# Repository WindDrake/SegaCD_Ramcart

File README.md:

# SegaCD_Ramcart
 Sega Genesis/Megadrive CD Back-up RAM Cart

 Design done in Kicad 5.1.10 with Digikey libraries. If you want to edit it, you'll need those libraries as well as these files.

 Board tested working 9/3/21 after fixing A20/A22 accidental swap @ U4.

 PCB revision 1.1 has this fixed.
 PCB revision 1.2 adds R2 to make sure the SRAM goes into sleep mode. The BOM has also changed.

 RAM Cart tested 9/3 with Dark Wizard and does not have the save corruption issue that the Castlemania Ultra cart has.

 CSV Format BOM & Gerbers added 10/30/21.

 If you have an Etsy/eBay/Aliexpress/etc. cartridge and are experiencing low battery life, you'll need to swap parts at R1, D1, and U2 with the parts listed in the current BOM. You'll also need to add a 10k resistor from U2 Pin 22 to D1 Pin 3 (the single pin on top).

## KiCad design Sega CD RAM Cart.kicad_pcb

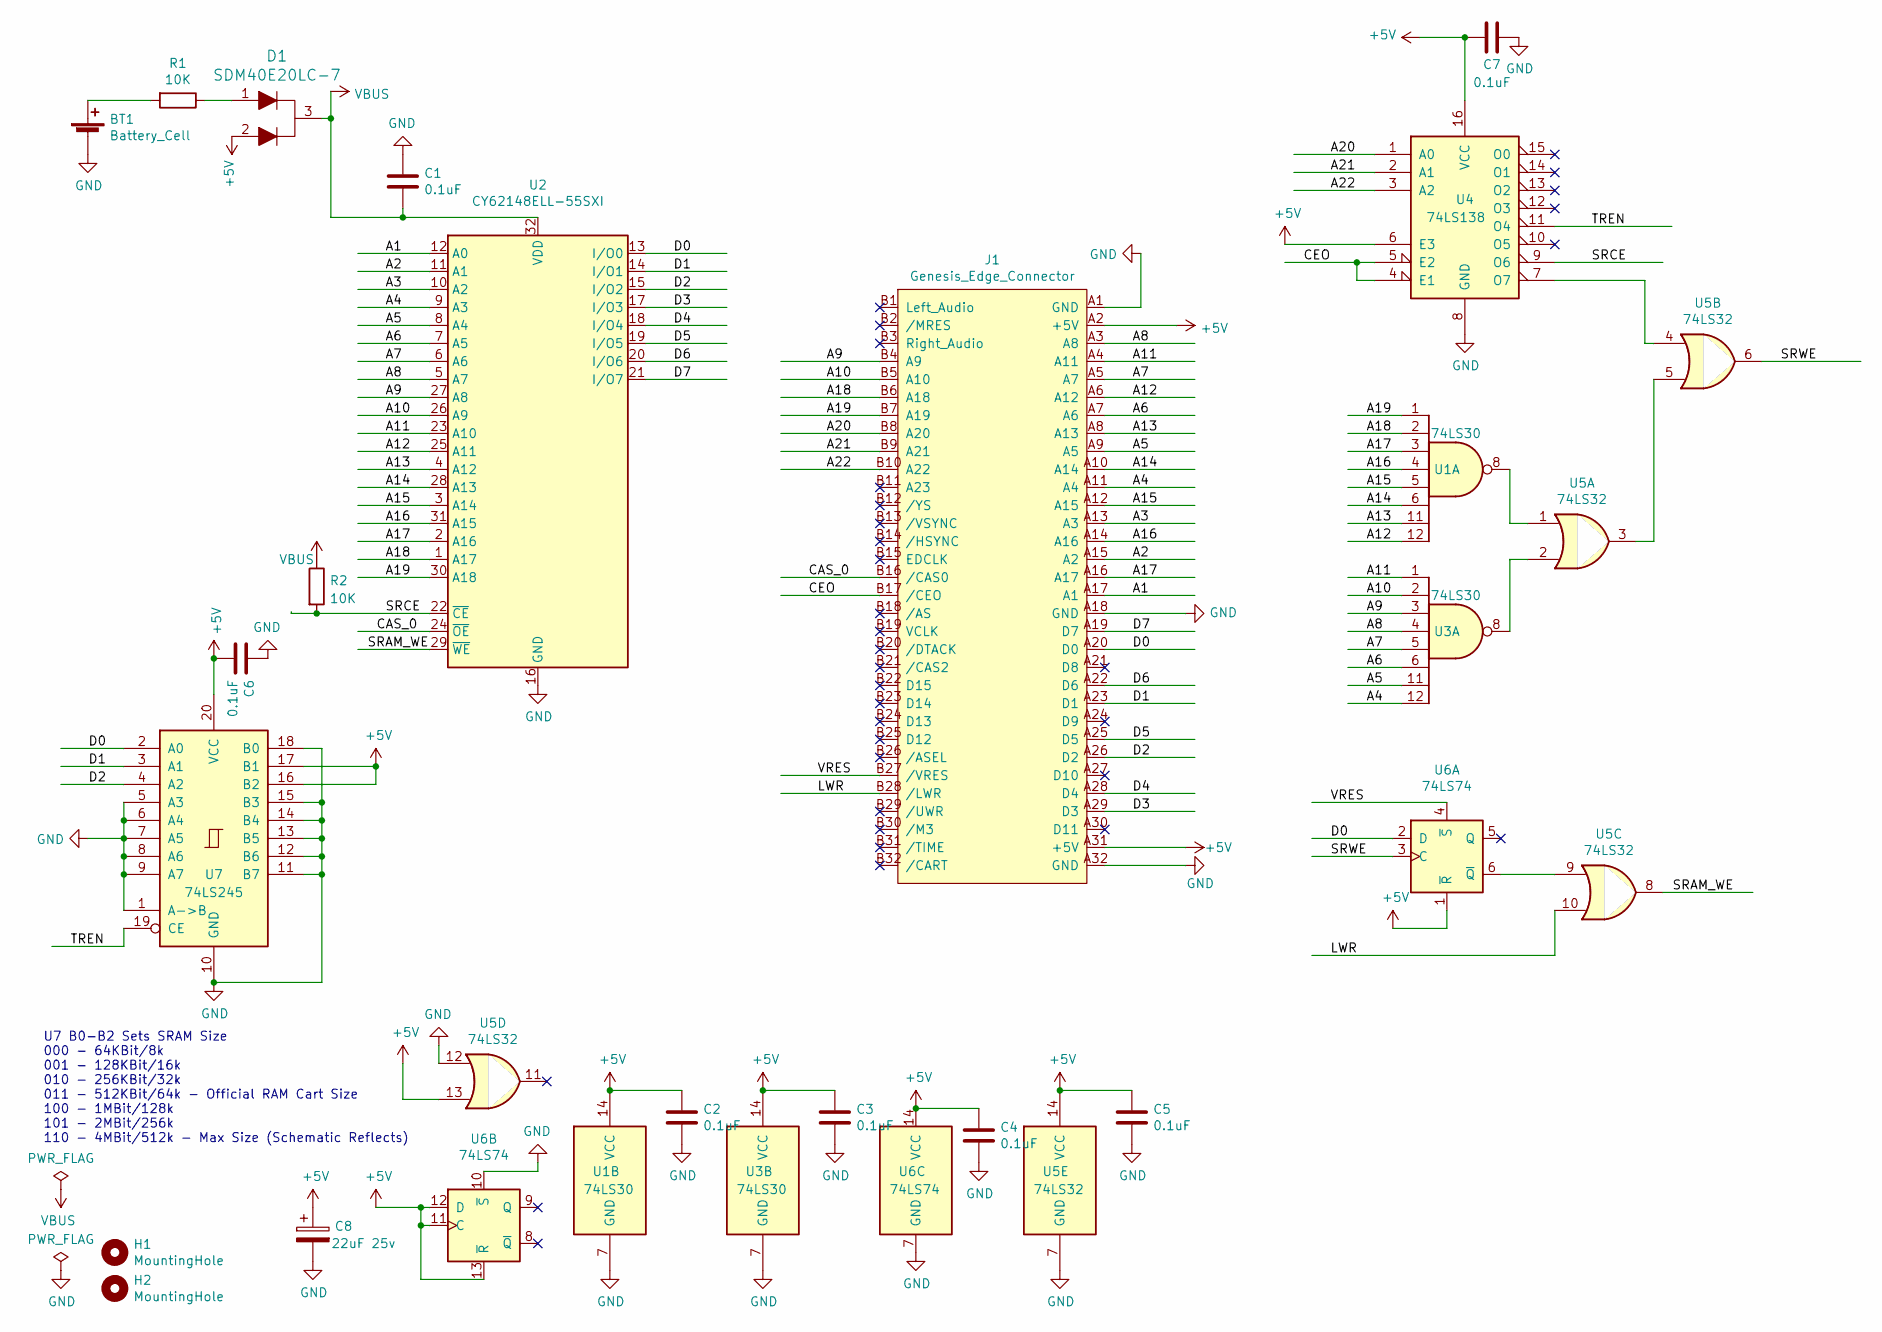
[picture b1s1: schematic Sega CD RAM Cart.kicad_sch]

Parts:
BT1: Battery_Cell; BAT_BU2450SM-JJ-G; Digikey PN BU2450SM-JJ-GTR
C1, C2, C3, C4, C5, C6, C7: 0.1uF; C_1206_3216Metric_Pad1.33x1.80mm_HandSolder; Digikey PN C1206C104K4RACTU
C8: 22uF 25v; CP_Radial_D5.0mm_P2.00mm; Digikey PN 25ML22MEFC5X5
D1: SDM40E20LC-7; SOT-23-3; Digikey PN SDM40E20LC-7
H1, H2: MountingHole; MountingHole_6.2mm
J1: Genesis_Edge_Connector; Genesis_Card_Edge
R1, R2: 10K; R_0805_2012Metric_Pad1.20x1.40mm_HandSolder; Digikey PN RMCF0805FT10K0
U1, U3: 74LS30; SOIC-14_W3.9mm; Digikey PN SN74LS30DR
U2: CY62148ELL-55SXI; SSOP-32_11.305x20.495mm_P1.27mm; Digikey PN CY62148ELL-55SXI
U4: 74LS138; SOIC-16_W3.90mm; Digikey PN SN74LS138DR
U5: 74LS32; SOIC-14_W3.9mm; Digikey PN SN74LS32DR
U6: 74LS74; SOIC-14_W3.9mm; Digikey PN SN74LS74ADR
U7: 74LS245; SSOP-20_W5.3mm; Digikey PN SN74LS245DBR

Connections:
+5V: C2.1, C3.1, C4.1, C5.1, C6.2, C7.2, C8.1, D1.2, J1.A2 (+5V), J1.A31 (+5V), U1.14 (VCC), U3.14 (VCC), U4.6 (E3), U4.16 (VCC), U5.13, U5.14 (VCC), U6.1 (~R), U6.11 (C), U6.12 (D), U6.13 (~R), U6.14 (VCC), U7.16 (B2), U7.17 (B1), U7.20 (VCC)
/A1: J1.A17 (A1), U2.12 (A0)
/A2: J1.A15 (A2), U2.11 (A1)
/A3: J1.A13 (A3), U2.10 (A2)
/A4: J1.A11 (A4), U2.9 (A3), U3.12
/A5: J1.A9 (A5), U2.8 (A4), U3.11
/A6: J1.A7 (A6), U2.7 (A5), U3.6
/A7: J1.A5 (A7), U2.6 (A6), U3.5
/A8: J1.A3 (A8), U2.5 (A7), U3.4
/A9: J1.B4 (A9), U2.27 (A8), U3.3
/A10: J1.B5 (A10), U2.26 (A9), U3.2
/A11: J1.A4 (A11), U2.23 (A10), U3.1
/A12: J1.A6 (A12), U1.12, U2.25 (A11)
/A13: J1.A8 (A13), U1.11, U2.4 (A12)
/A14: J1.A10 (A14), U1.6, U2.28 (A13)
/A15: J1.A12 (A15), U1.5, U2.3 (A14)
/A16: J1.A14 (A16), U1.4, U2.31 (A15)
/A17: J1.A16 (A17), U1.3, U2.2 (A16)
/A18: J1.B6 (A18), U1.2, U2.1 (A17)
/A19: J1.B7 (A19), U1.1, U2.30 (A18)
/A20: J1.B8 (A20), U4.1 (A0)
/A21: J1.B9 (A21), U4.2 (A1)
/A22: J1.B10 (A22), U4.3 (A2)
/CAS_0: J1.B16 (/CAS0), U2.24 (~OE)
/CEO: J1.B17 (/CEO), U4.4 (E1), U4.5 (E2)
/D0: J1.A20 (D0), U2.13 (I/O0), U6.2 (D), U7.2 (A0)
/D1: J1.A23 (D1), U2.14 (I/O1), U7.3 (A1)
/D2: J1.A26 (D2), U2.15 (I/O2), U7.4 (A2)
/D3: J1.A29 (D3), U2.17 (I/O3)
/D4: J1.A28 (D4), U2.18 (I/O4)
/D5: J1.A25 (D5), U2.19 (I/O5)
/D6: J1.A22 (D6), U2.20 (I/O6)
/D7: J1.A19 (D7), U2.21 (I/O7)
/LWR: J1.B28 (/LWR), U5.10
/SRAM_WE: U2.29 (~WE), U5.8
/SRCE: R2.2, U2.22 (~CE), U4.9 (O6)
/SRWE: U5.6, U6.3 (C)
/TREN: U4.11 (O4), U7.19 (CE)
/VRES: J1.B27 (/VRES), U6.4 (~S)
GND: BT1.N (-), C1.1, C2.2, C3.2, C4.2, C5.2, C6.1, C7.1, C8.2, J1.A1 (GND), J1.A18 (GND), J1.A32 (GND), U1.7 (GND), U2.16 (GND), U3.7 (GND), U4.8 (GND), U5.7 (GND), U5.12, U6.7 (GND), U6.10 (~S), U7.1 (A->B), U7.5 (A3), U7.6 (A4), U7.7 (A5), U7.8 (A6), U7.9 (A7), U7.10 (GND), U7.11 (B7), U7.12 (B6), U7.13 (B5), U7.14 (B4), U7.15 (B3), U7.18 (B0)
unnamed: BT1.P (+), R1.2
unnamed: D1.1, R1.1
unnamed: U1.8, U5.1
unnamed: U3.8, U5.2
unnamed: U4.7 (O7), U5.4
unnamed: U5.3, U5.5
unnamed: U5.9, U6.6 (~Q)
VBUS: C1.2, D1.3, R2.1, U2.32 (VDD)

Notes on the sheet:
U7 B0-B2 Sets SRAM Size 000 - 64KBit/8k 001 - 128KBit/16k 010 - 256KBit/32k 011 - 512KBit/64k - Official RAM Cart Size 100 - 1MBit/128k 101 - 2MBit/256k 110 - 4MBit/512k - Max Size (Schematic Reflects)

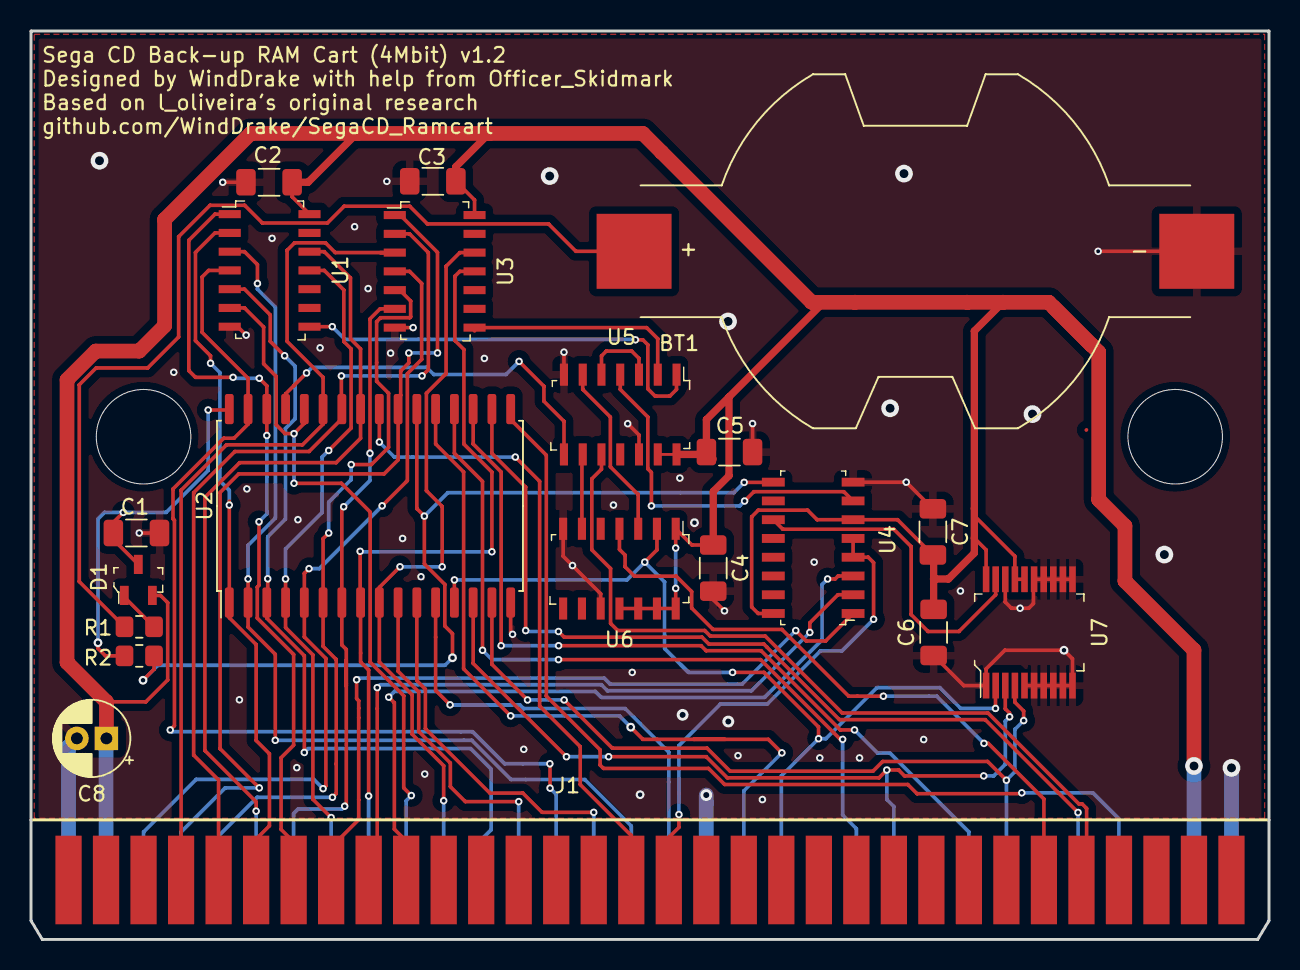
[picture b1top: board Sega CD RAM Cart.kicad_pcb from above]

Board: 2 copper layers, 83.8 x 61.5 mm, 22 parts (0 on the bottom side), 48 nets.

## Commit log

2021-08-20 First upload.
2021-08-20 Finalizing design.
2021-08-20 More cleanup.
    Boards approaching final rev. Added OSHW logos & other stuff.
2021-08-21 Last Rev - PCB's Ordered
    Full 1.0 revision is complete. PCB's ordered today through OSHPark.
2021-09-01 Board tweaks.
    U5D OR Gate inputs tied up so they don't float. No other changes.
2021-09-03 Board Updates (+Board tested!)
    Removed unneeded files, fixed A20/A22 swap @ U4. Boards tested working today after cut & jumper on the real PCB's.
2021-09-04 BOM Fix
    Realized I specified a 1206 resistor instead of 0805. Fixed the BOM. Also added an HTML exported BOM for easy reading.
2021-10-30 Create Sega CD RAM Cart.csv
    Added CSV BOM.
2021-10-30 Added Gerbers.
2021-11-13 Final label & BOM.
    Final label has been completed (.PSD format) and a spelling error in the .xml BOM. Project at this point is complete.
2025-12-14 1.2 Overhaul
    Changed SRAM, protection diode, protection resistor to fix battery lifetime problem. Added R2 to fix lack of sleep mode.
2025-12-14 1.2 Update
